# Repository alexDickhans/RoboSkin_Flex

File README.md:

# Flexible robotic skin

This project made by Alex and the HIRO lab to more easily make capacitive touch robotic skin using flexible PCBs.

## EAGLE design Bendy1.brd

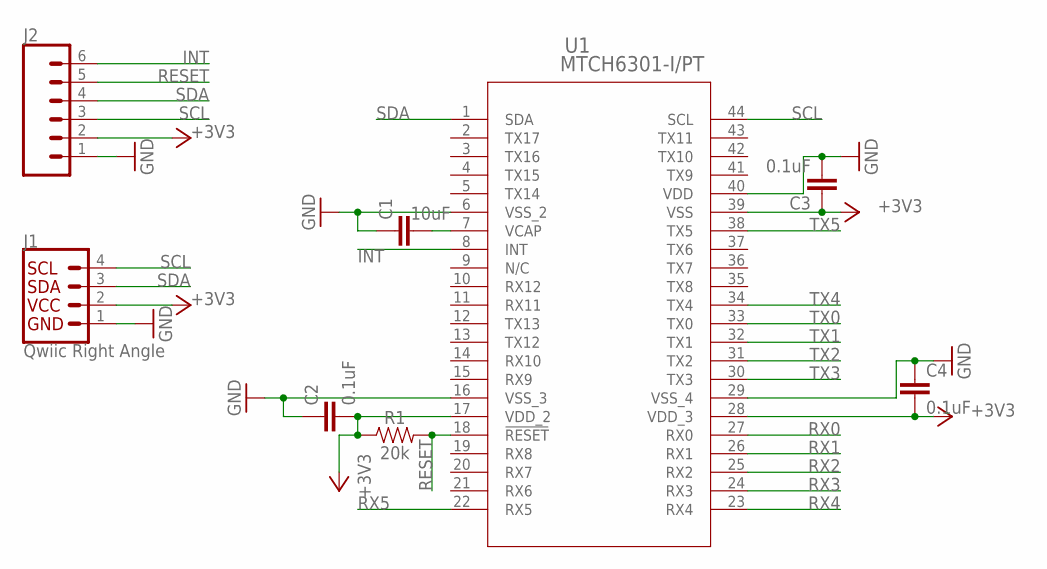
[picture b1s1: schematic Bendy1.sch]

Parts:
C1: 10uF; 0603
C2, C3: 0.1uF; 0603
C4: 0.1uF; 0402
J1: Qwiic Right Angle; JST04_1MM_RA
J2: CONN_06NO_SILK_FEMALE_PTH; 1X06_NO_SILK
R1: 20k; 0603
U1: MTCH6301-I/PT; TQFP44_10X10MC_MCH

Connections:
+3V3: C2.2, C3.1, C4.2, J1.2, J2.2, R1.1, U1.17 (VDD_2), U1.28 (VDD_3), U1.39 (VSS)
GND: C1.1, C2.1, C3.2, C4.1, J1.1, J2.1, U1.6 (VSS_2), U1.16 (VSS_3), U1.29 (VSS_4), U1.40 (VDD)
INT: J2.6, U1.8 (INT)
unnamed: C1.2, U1.7 (VCAP)
RESET: J2.5, R1.2, U1.18 (!RESET)
RX0: U1.27 (RX0)
RX1: U1.26 (RX1)
RX2: U1.25 (RX2)
RX3: U1.24 (RX3)
RX4: U1.23 (RX4)
RX5: U1.22 (RX5)
SCL: J1.4, J2.3, U1.44 (SCL)
SDA: J1.3, J2.4, U1.1 (SDA)
TX0: U1.33 (TX0)
TX1: U1.32 (TX1)
TX2: U1.31 (TX2)
TX3: U1.30 (TX3)
TX4: U1.34 (TX4)
TX5: U1.38 (TX5)

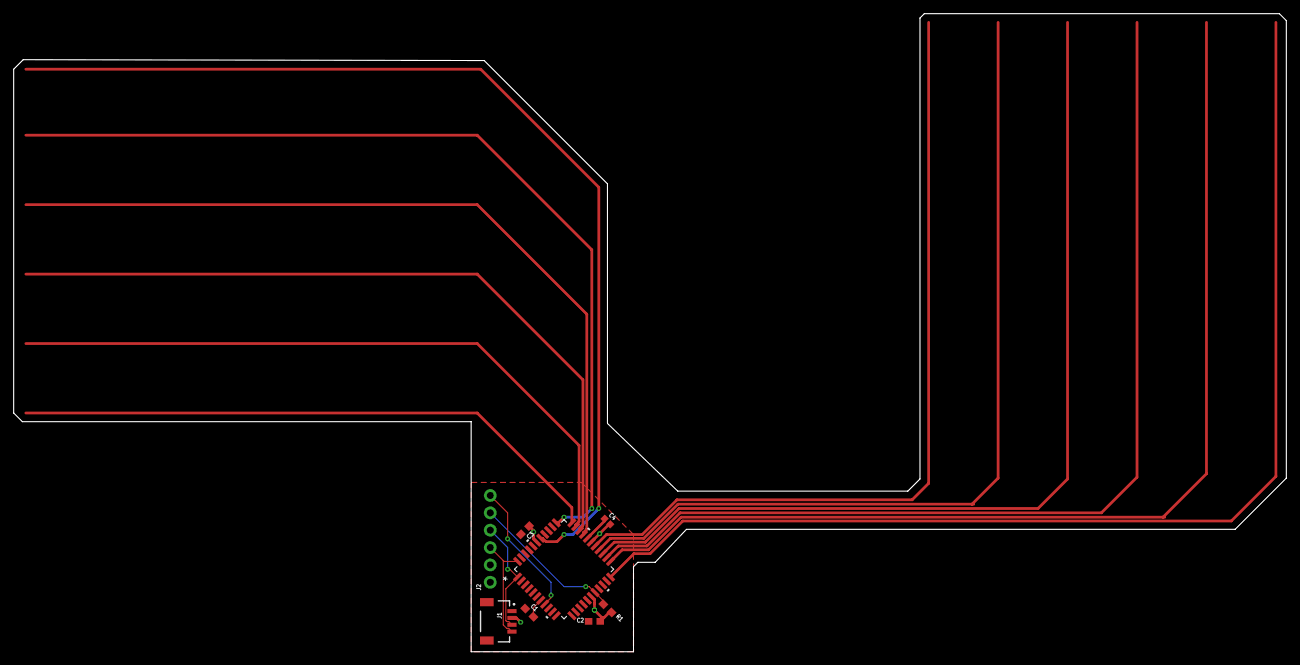
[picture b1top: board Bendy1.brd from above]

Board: 2 copper layers, 186.2 x 93.3 mm, 8 parts (0 on the bottom side), 7 nets.

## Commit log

2024-04-03 Almost ready to route cut lines

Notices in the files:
parts and their libraries:
SparkFun-Capacitors: Licensing: Creative Commons ShareAlike 4.0 International - https://creativecommons.org/licenses/by-sa/4.0
COPYRIGHT: Copyright (C) 2024 Ultra Librarian. All rights reserved.
